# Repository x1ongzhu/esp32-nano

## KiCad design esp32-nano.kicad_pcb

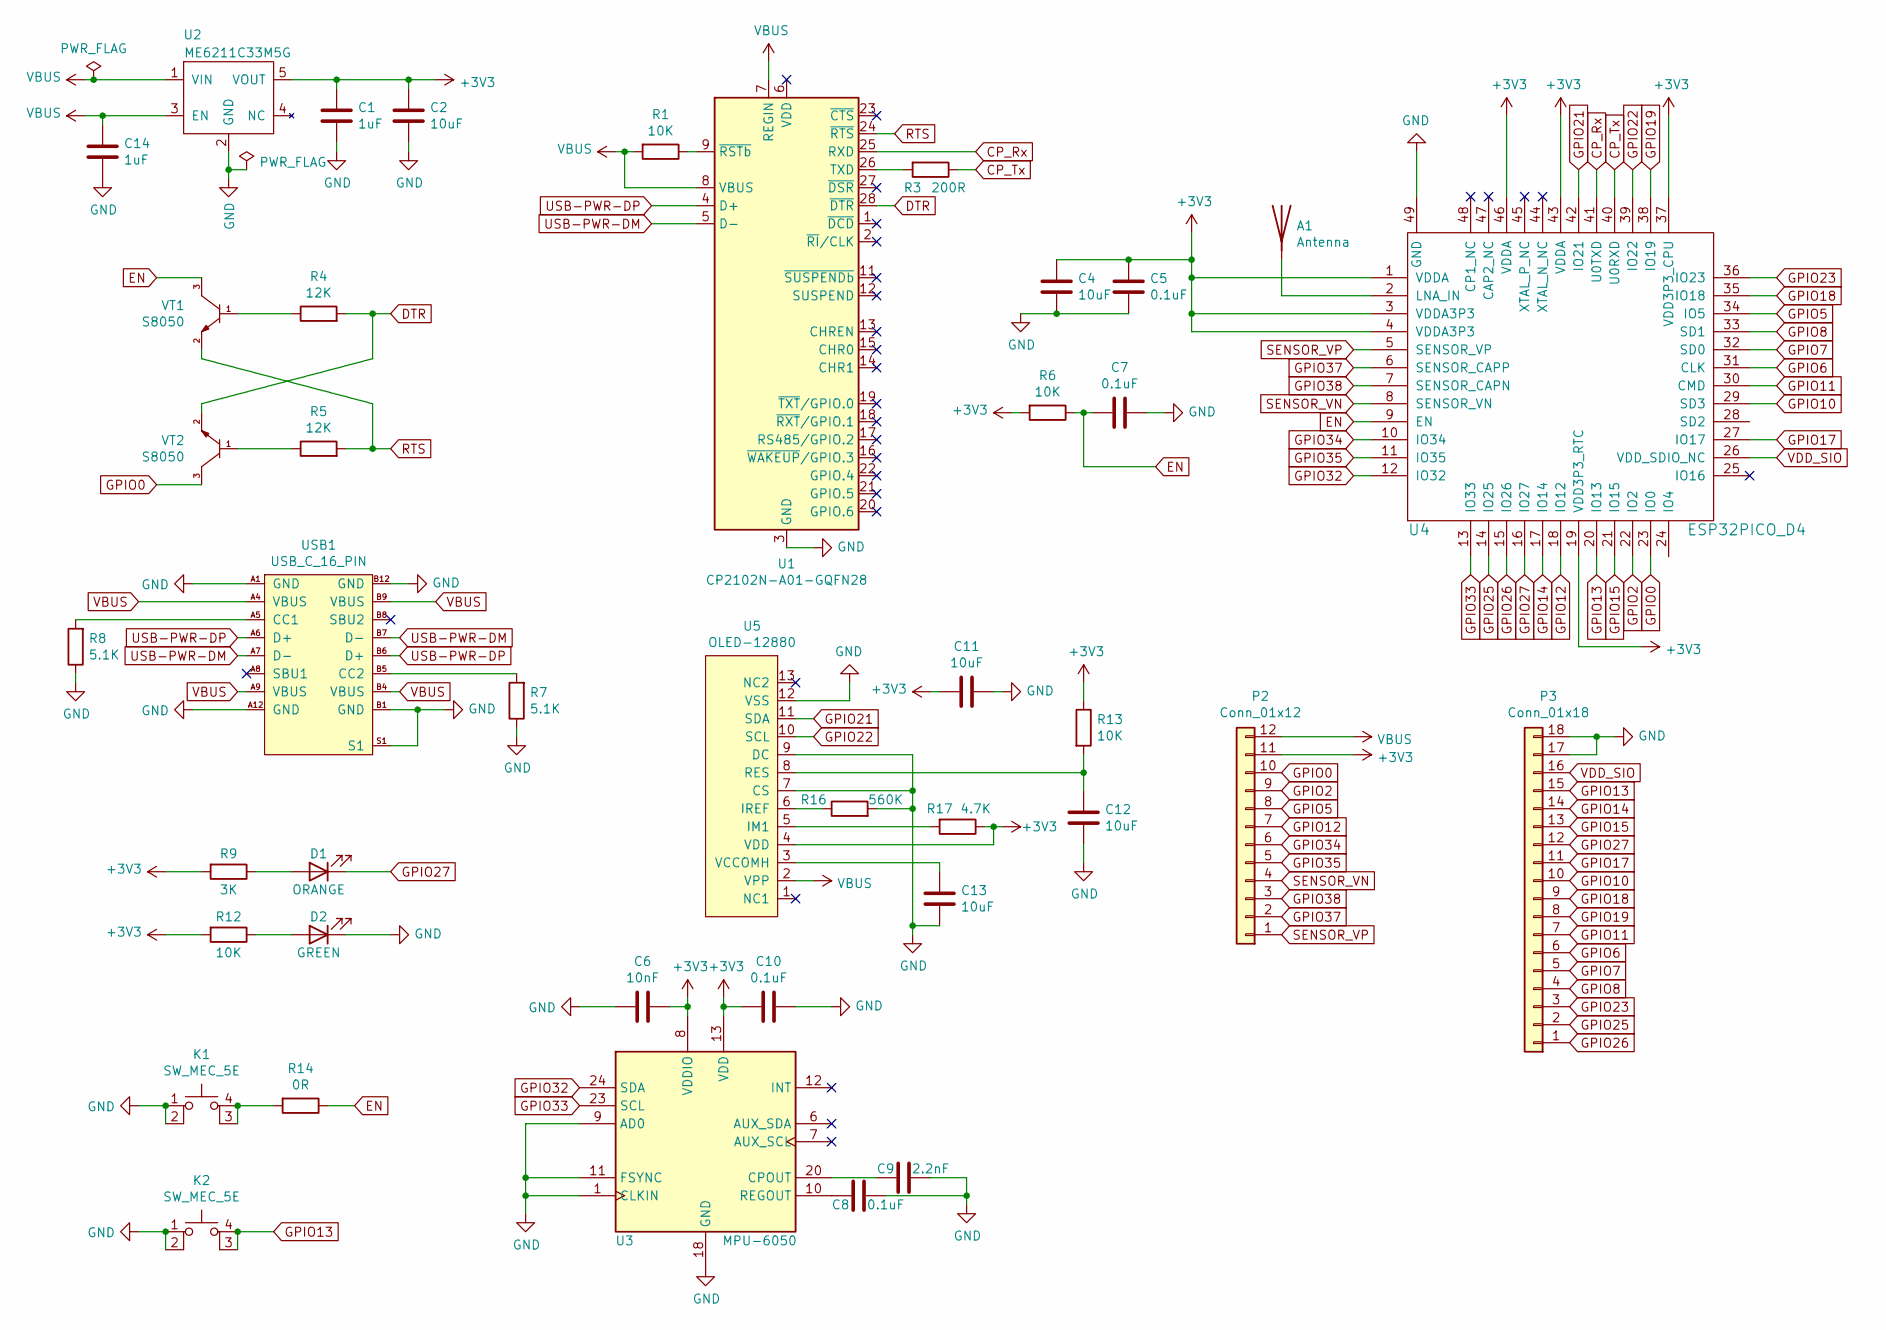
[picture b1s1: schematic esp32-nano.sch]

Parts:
A1: Antenna; CA-C03
C1, C14: 1uF; C_0402_1005Metric
C2, C4, C11, C12, C13: 10uF; C_0402_1005Metric
C5, C7, C8, C10: 0.1uF; C_0402_1005Metric
C6: 10nF; C_0402_1005Metric
C9: 2.2nF; C_0402_1005Metric
D1: ORANGE; LED_0402_1005Metric
D2: GREEN; LED_0402_1005Metric
K1, K2: SW_MEC_5E; SKSC_NO_HOLE
P2: Conn_01x12; PinHeader_1x12_P2.54mm
P3: Conn_01x18; PinHeader_1x18_P2.54mm
R1, R6, R12, R13: 10K; R_0402_1005Metric
R3: 200R; R_0402_1005Metric
R4, R5: 12K; R_0402_1005Metric
R7, R8: 5.1K; R_0402_1005Metric
R9: 3K; R_0402_1005Metric
R14: 0R; R_0402_1005Metric
R16: 560K; R_0402_1005Metric
R17: 4.7K; R_0402_1005Metric
U1: CP2102N-A01-GQFN28; QFN-28-1EP_5x5mm_P0.5mm_EP3.35x3.35mm
U2: ME6211C33M5G; SOT-23-5; Manufacturer_Part_Number ME6211C33M5G
U3: MPU-6050; InvenSense_QFN-24_4x4mm_P0.5mm
U4: ESP32PICO_D4; ESP32_PICO_D4
U5: OLED-12880
USB1: USB_C_16_PIN; USB_C_Receptacle_HRO_TYPE-C-31-M-12
VT1, VT2: S8050; SOT-23

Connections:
+3V3: C1.1, C2.1, C4.1, C5.1, C6.1, C10.2, C11.2, P2.11, R6.2, R9.2, R12.2, R13.1, R17.1, U2.5 (VOUT), U3.8 (VDDIO), U3.13 (VDD), U4.1 (VDDA), U4.3 (VDDA3P3), U4.4 (VDDA3P3), U4.19 (VDD3P3_RTC), U4.37 (VDD3P3_CPU), U4.43 (VDDA), U4.46 (VDDA), U5.4 (VDD)
CP_Rx: U1.25 (RXD), U4.41 (U0TXD)
CP_Tx: R3.1, U4.40 (U0RXD)
DTR: R4.2, U1.28 (~DTR), VT2.2
EN: C7.1, R6.1, R14.1, U4.9 (EN), VT1.3
GND: C1.2, C2.2, C4.2, C5.2, C6.2, C7.2, C8.1, C9.1, C10.1, C11.1, C12.2, C13.2, C14.2, D2.1 (K), K1.1, K1.2, K2.1, K2.2, P3.17, P3.18, R7.1, R8.1, R16.2, U1.3 (GND), U1.29 (GND), U2.2 (GND), U3.1 (CLKIN), U3.9 (AD0), U3.11 (FSYNC), U3.18 (GND), U4.49 (GND), U5.7 (CS), U5.9 (DC), U5.12 (VSS), USB1.A1 (GND), USB1.A12 (GND), USB1.B1 (GND), USB1.B12 (GND), USB1.S1
GPIO0: P2.10, U4.23 (IO0), VT2.3
GPIO2: P2.9, U4.22 (IO2)
GPIO5: P2.8, U4.34 (IO5)
GPIO6: P3.6, U4.31 (CLK)
GPIO7: P3.5, U4.32 (SD0)
GPIO8: P3.4, U4.33 (SD1)
GPIO10: P3.10, U4.29 (SD3)
GPIO11: P3.7, U4.30 (CMD)
GPIO12: P2.7, U4.18 (IO12)
GPIO13: K2.3 (K), K2.4 (A), P3.15, U4.20 (IO13)
GPIO14: P3.14, U4.17 (IO14)
GPIO15: P3.13, U4.21 (IO15)
GPIO17: P3.11, U4.27 (IO17)
GPIO18: P3.9, U4.35 (IO18)
GPIO19: P3.8, U4.38 (IO19)
GPIO21: U4.42 (IO21), U5.11 (SDA)
GPIO22: U4.39 (IO22), U5.10 (SCL)
GPIO23: P3.3, U4.36 (IO23)
GPIO25: P3.2, U4.14 (IO25)
GPIO26: P3.1, U4.15 (IO26)
GPIO27: D1.1 (K), P3.12, U4.16 (IO27)
GPIO32: U3.24 (SDA), U4.12 (IO32)
GPIO33: U3.23 (SCL), U4.13 (IO33)
GPIO34: P2.6, U4.10 (IO34)
GPIO35: P2.5, U4.11 (IO35)
GPIO37: P2.2, U4.6 (SENSOR_CAPP)
GPIO38: P2.3, U4.7 (SENSOR_CAPN)
unnamed: A1.1, U4.2 (LNA_IN)
unnamed: C8.2, U3.10 (REGOUT)
unnamed: C9.2, U3.20 (CPOUT)
unnamed: C12.1, R13.2, U5.8 (RES)
unnamed: C13.1, U5.3 (VCCOMH)
unnamed: D1.2 (A), R9.1
unnamed: D2.2 (A), R12.1
unnamed: K1.3 (K), K1.4 (A), R14.2
unnamed: R1.1, U1.9 (~RSTb)
unnamed: R3.2, U1.26 (TXD)
unnamed: R4.1, VT1.1
unnamed: R5.1, VT2.1
unnamed: R7.2, USB1.B5 (CC2)
unnamed: R8.2, USB1.A5 (CC1)
unnamed: R16.1, U5.6 (IREF)
unnamed: R17.2, U5.5 (IM1)
RTS: R5.2, U1.24 (~RTS), VT1.2
SENSOR_VN: P2.4, U4.8 (SENSOR_VN)
SENSOR_VP: P2.1, U4.5 (SENSOR_VP)
USB-PWR-DM: U1.5 (D-), USB1.A7 (D-), USB1.B7 (D-)
USB-PWR-DP: U1.4 (D+), USB1.A6 (D+), USB1.B6 (D+)
VBUS: C14.1, P2.12, R1.2, U1.7 (REGIN), U1.8 (VBUS), U2.1 (VIN), U2.3 (EN), U5.2 (VPP), USB1.A4 (VBUS), USB1.A9 (VBUS), USB1.B4 (VBUS), USB1.B9 (VBUS)
VDD_SIO: P3.16, U4.26 (VDD_SDIO_NC)

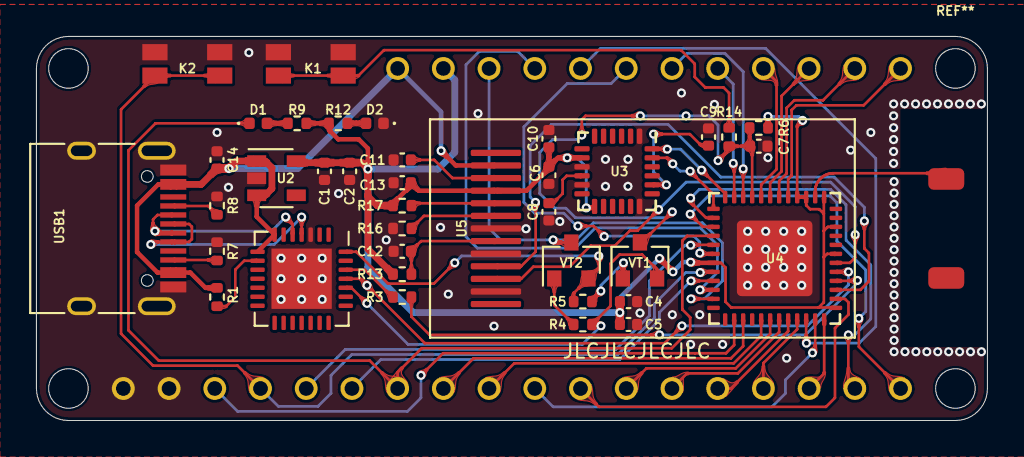
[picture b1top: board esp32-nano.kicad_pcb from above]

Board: 2 copper layers, 52.8 x 21.3 mm, 41 parts (0 on the bottom side), 56 nets.

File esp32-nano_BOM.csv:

"Comment","Description","Designator","Footprint","LibRef","Pins","Quantity","PartNumber","url",
"Antenna","desc","A1,","CA-C03","libref","2","1","","",
"1uF","desc","C1,C14,","C_0402_1005Metric","libref","2","2","","",
"10uF","desc","C2,C4,C11,C12,C13,","C_0402_1005Metric","libref","2","5","","",
"0.1uF","desc","C5,C7,C8,C10,","C_0402_1005Metric","libref","2","4","","",
"10nF","desc","C6,","C_0402_1005Metric","libref","2","1","","",
"2.2nF","desc","C9,","C_0402_1005Metric","libref","2","1","","",
"ORANGE","desc","D1,","LED_0402_1005Metric","libref","2","1","","",
"GREEN","desc","D2,","LED_0402_1005Metric","libref","2","1","","",
"SW_MEC_5E","desc","K1,K2,","SKSCLCE010","libref","4","2","","",
"10K","desc","R1,R6,R9,R12,R13,","R_0402_1005Metric","libref","2","5","","",
"200R","desc","R3,","R_0402_1005Metric","libref","2","1","","",
"12K","desc","R4,R5,","R_0402_1005Metric","libref","2","2","","",
"5.1K","desc","R7,R8,","R_0402_1005Metric","libref","2","2","","",
"1K","desc","R14,","R_0402_1005Metric","libref","2","1","","",
"560K","desc","R16,","R_0402_1005Metric","libref","2","1","","",
"4.7K","desc","R17,","R_0402_1005Metric","libref","2","1","","",
"CP2102N-A01-GQFN28","desc","U1,","QFN-28-1EP_5x5mm_P0.5mm_EP3.35x3.35mm","libref","38","1","","",
"ME6211C33M5G","desc","U2,","SOT-23-5","libref","5","1","","",
"MPU-6050","desc","U3,","InvenSense_QFN-24_4x4mm_P0.5mm","libref","24","1","","",
"ESP32PICO_D4","desc","U4,","ESP32_PICO_D4","libref","64","1","","",
"OLED-12880","desc","U5,","OLED-12880","libref","13","1","","",
"S8050","desc","VT1,VT2,","SOT-23","libref","3","2","","",
"Through Hole Items ",
"Conn_01x12","desc","P2,","12pin","libref","12","1","","",
"Conn_01x18","desc","P3,","18pin","libref","18","1","","",
"USB_C_16_PIN","desc","USB1,","USB_C_Receptacle_HRO_TYPE-C-31-M-12","libref","22","1","","",
"MountingHole_2.2mm_M2","desc","REF**,REF**,REF**,REF**,","MountingHole_2.2mm_M2","libref","1","4","","",

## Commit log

2021-09-26 .gitignore
2021-10-24 引出psram
